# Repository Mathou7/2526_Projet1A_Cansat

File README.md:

# 2526_Projet1A_Cansat

## A Propos de la CanSat
Le concours CanSat, organisé chaque année dans le cadre du C’Space par le CNES et Planète Sciences, propose aux étudiants de concevoir, construire et faire voler un véritable mini-satellite de la taille d’une canette.
Lancé depuis un drone à environ 150 mètres d’altitude, le CanSat doit réaliser une mission scientifique ou technique en chute contrôlée, tout en respectant des contraintes strictes de taille, de masse et d’autonomie et en réalisant les missions imposées.
Ce concours permet aux étudiants d’aborder concrètement l’ensemble des étapes d’un projet spatial : conception système, intégration électronique, programmation embarquée, gestion de l’énergie et tests.

# L'équipe
- Marin.P
- Pierre-Antoine.R
- Lucas.G
- Arnaud.M
- Mathis.B.

## Liste des fonctionnalités
- Mesure de la pression grâce au baromètre
- Mesure de la distance grâce au TOF
- Utilisation d'un moteur pour actionner un mécanisme
- Prise de vidéo à l'aide de la caméra
- Interrupteur général permettant d'allumer et éteindre la canette

## Choix des composants
- Microcontroleur (stm32g431kbt)
- Baromètre (bnp581)
- Moteur brushless (GA12-N20)
- Centrale inertielle (abandonné) 
- Time of Lights (abandonné)
- Caméra (VC0706)
- Interrupteur

## PCB

PCB à quatre couches constitué de
- STM32G431KBT
- Régulateur 6.5-36V vers 5V
- Régulateur 5V vers 3.3V
- Driver Moteur
- Baromètre
- Interface Jack
- Interface Moteur
- Interface Bouton
- Interface Camera
- Connecteur ST

## Difficultés

Approvisionnement en composants
Nous n'avons pas reçu exactement les composants que l'on souhaitait au départ notamment la caméra qui devait enregistrer les images pendant la chute. Celle à laquelle nous avons eu accès transmet les images par onde radio, permettant de voir directement les images sur un écran extérieur à la canette.

Forme restrictive
La forme particulière du PCB imposée par le volume restreint de la canette et le système d'ouverture du parachute a constitué un frein considérable à la conception du PCB.

Code
Une étude détaillée du fonctionnement du baromètre a été nécessaire afin de coder les différentes fonctions permettant d'aboutir au calcul de l'altitude, ce qui a été très chronophage 

Conception de la canette
Le système d'ouverture du parachute a été le principal défi de conception nous forçant à modifier l'architecture de notre canette.

## Solutions trouvées

Les composants 
Pour la caméra nous avons trouvé une caméra avec un fonctionnement différent de celle initialement prévue.
Nous avons reçu le baromètre déjà soudé sur un PCB alors que nous avions demandé le baromètre seul, nous l'avons donc désoudé pour le resouder sur notre PCB.
En attendant la livraison du connecteur pour la batterie (JST-SH) nous avons soudé directement la batterie à l'interface prévue initialement pour le connecteur.

Conception de la canette 
Nous avons séparé notre canette en 2 espaces : une partie acceuillant le PCB et ses différents composants dont le moteur et une partie dans laquelle se trouve le parachute.
Le système d'ouverture fonctionne gràce à 2 goupilles qui maintiennent la partie contenant le parachute et la patie contenant le PCB ensemble. Ces 2 goupilles sont reliées par des fils au moteur qui en tournant va enrouler ces fils autour de son axe et les libérer. Le capuchon dans lequel se trouve le parachute va donc se détacher pour laisser le parachute sortir et se déployer. Le capuchon une fois détaché du reste de la canette reste relié à celle-ci via un autre fil nous permettant de respecter une exigeance imposée par le concours: aucune partie de la canette ne doit tomber au sol sans être ralentie.

## Partie Méca

Partie contenant le PCB et tout les éléments qui y sont reliés :

Opercule fermant la partie PCB qui maintient la partie parachute :

Corps du capuchon contenant le parachute : 

Opercule fermant le capuchon du parachute :

## Bilan des fonctionnalités

Test du bouton permettant d'allumer la LED

https://github.com/user-attachments/assets/89bd5818-fe06-4b41-a8be-61a60c13a220

Test du moteur

https://github.com/user-attachments/assets/85a999e9-10d9-4074-9609-f378fe4b467d

## Reflexion responsable 
Dans quelle mesure votre projet peut-il être intégré à des mesures d’adaptaton ou d’aténuaton du changement
climatque ?

Notre Cansat pourrait filmer un territoire pendant le largage et nous y montrer une évolution. Par exemple, face à une forêt, voir l'effet d'une déforestation ou d'une dégradation du territoire.

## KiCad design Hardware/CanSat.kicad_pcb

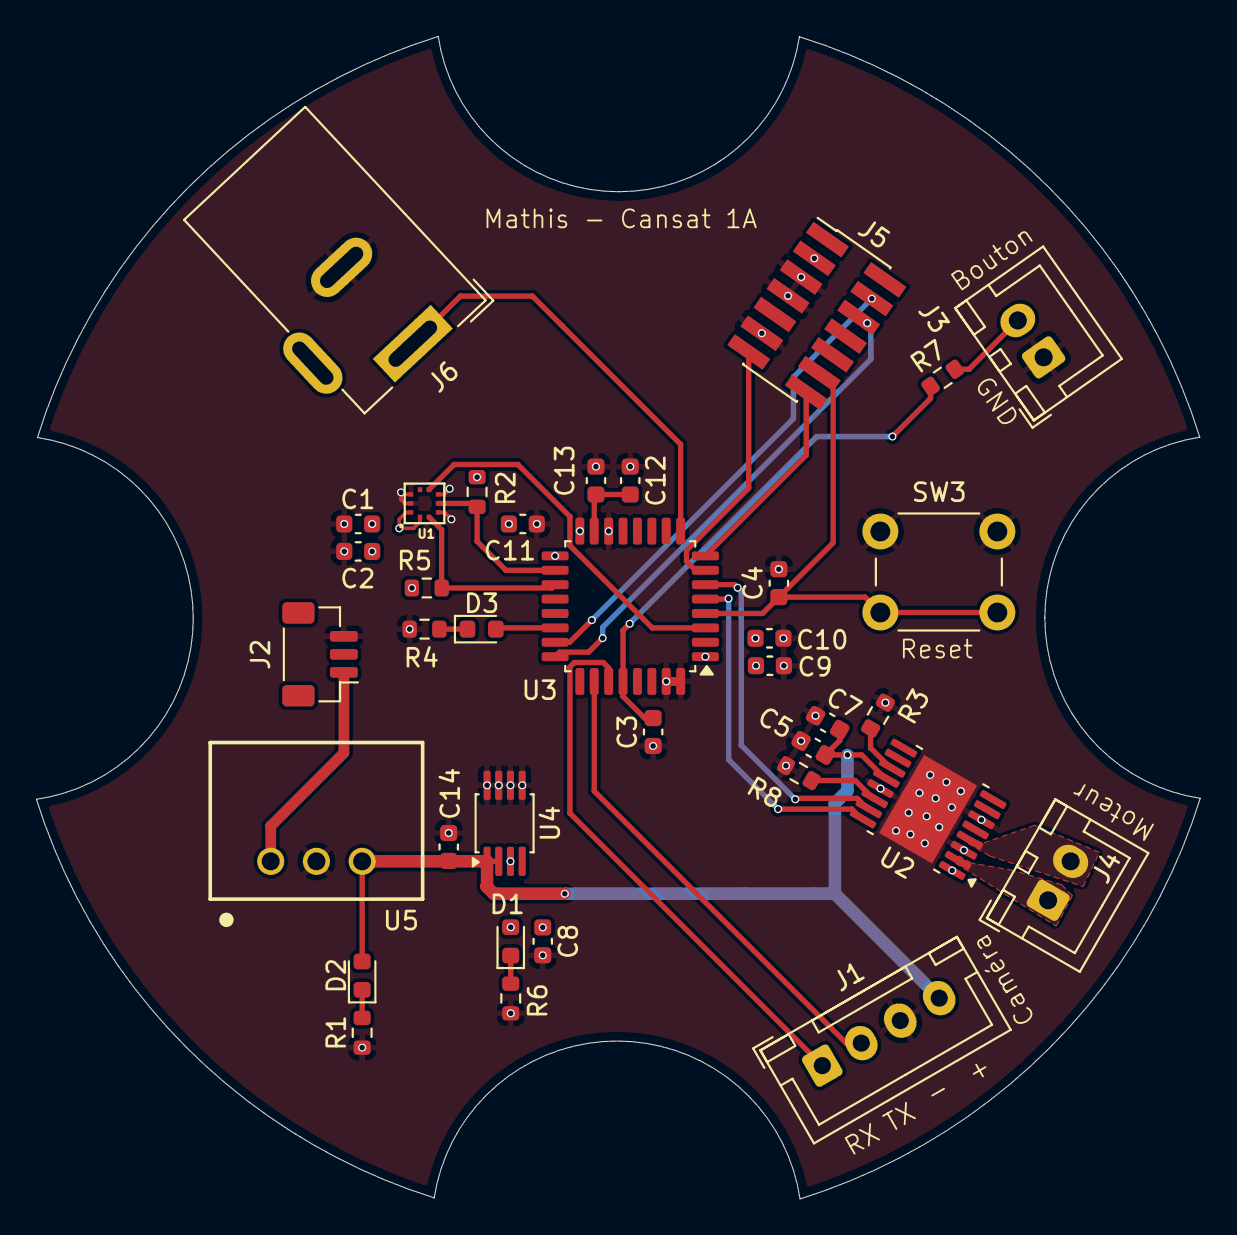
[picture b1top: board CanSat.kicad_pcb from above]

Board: 4 copper layers, 64.7 x 64.6 mm, 36 parts (0 on the bottom side), 28 nets.

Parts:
C1, C2, C3, C4, C5, C10, C11: 100nF; C_0603_1608Metric
C7: 10uF; C_0603_1608Metric
C8, C13, C14: 1uF; C_0603_1608Metric
C9: 4.7uF; C_0603_1608Metric
C12: 10nF; C_0603_1608Metric
D1, D2, D3: LED_Small; LED_0603_1608Metric
J1: Conn_01x04; JST_XH_B4B-XH-A_1x04_P2.50mm_Vertical
J2: Conn_01x03; JST_SH_BM03B-SRSS-TB_1x03-1MP_P1.00mm_Vertical
J3, J4: Conn_01x02; JST_XH_B2B-XH-A_1x02_P2.50mm_Vertical
J5: Conn_ST_STDC14; PinHeader_2x07_P1.27mm_Vertical_SMD
J6: Barrel_Jack_Switch; BarrelJack_Wuerth_6941xx301002
R1, R5, R6: 1k; R_0603_1608Metric
R2, R3, R4, R8: 10k; R_0603_1608Metric
R7: 100; R_0603_1608Metric
SW3: SW_Push; SW_PUSH_6mm_H5mm
U1: BMP581
U2: DRV8833PWP; HTSSOP-16-1EP_4.4x5mm_P0.65mm_EP3.4x5mm_Mask2.46x2.31mm_The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
U3: STM32G431KBTx; LQFP-32_7x7mm_P0.8mm
U4: MIC5219-3.3YMM; MSOP-8_3x3mm_P0.65mm
U5: WPME-FDSM_SIP-3; WPME-FDSM_173010X78

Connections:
+3.3V: C1.2, C2.2, C8.1, C9.2, C10.2, C11.2, D1.2 (A), J5.3 (VCC), R2.2, R4.2, U1.1 (VDDIO), U1.10 (VDD), U2.1 (VREF), U3.1 (VDD), U3.17 (VDD), U4.3 (OUT)
+3.3VA: C12.2, C13.2, U3.15 (VDDA)
+5V: C5.2, C7.1, C14.1, D2.2 (A), J1.4, U2.12 (VM), U4.1 (EN), U4.2 (IN), U5.3
AIN1: U2.16 (AIN1), U3.5 (PA0)
AIN2: U2.15 (AIN2), U3.6 (PA1)
AOUT1: J4.1, U2.2 (AOUT1)
AOUT2: J4.2, U2.4 (AOUT2)
Bouton: C3.2, R7.1, U3.28 (PB5)
GND: C1.1, C2.1, C3.1, C4.2, C5.1, C7.2, C8.2, C9.1, C10.1, C11.1, C12.1, C13.1, C14.2, J1.3, J2.3, J3.1, J5.5 (GND), J5.7 (GND), J5.11 (GNDDetect), J6.2, R1.1, R3.2, R5.1, R6.1, R8.2, SW3.1, U1.3 (GND), U1.5 (SDO/ADR), U1.8 (GND), U1.9 (GND), U2.3 (GND), U2.6 (GND), U2.13 (GND), U2.17 (GND), U3.14 (VSSA), U3.16 (VSS), U3.31 (PB8), U3.32 (VSS), U4.5 (GND), U4.6 (GND), U4.7 (GND), U4.8 (GND), U5.2
INT: U1.6 (CSB), U3.3 (PF1)
JackIN: J6.1, U3.9 (PA4)
NRST: C4.1, J5.12 (~RST), SW3.2, U3.4 (PG10)
unnamed: D1.1 (K), R6.2
unnamed: D2.1 (K), R1.2
unnamed: D3.2 (A), U3.22 (PA12)
unnamed: D3.1 (K), R5.2
unnamed: J3.2, R7.2
unnamed: R8.1, U2.14 (AIPROPI)
unnamed: R3.1, U2.11 (BIPROPI)
RXCAM: J1.1, U3.27 (PB4)
SCL: R4.1, U1.2 (SCK/SCL), U3.19 (PA9)
SDA: R2.1, U1.4 (SDI/SDA), U3.18 (PA8)
SWCLK: J5.6 (JCLK/SWCLK), U3.24 (PA14)
SWDIO: J5.4 (JTMS/SWDIO), U3.23 (PA13)
TXCAM: J1.2, U3.26 (PB3)
VCP_RX: J5.13 (VCP_RX), U3.7 (PA2)
VCP_TX: J5.14 (VCP_TX), U3.8 (PA3)
VIN: J2.1, U5.1

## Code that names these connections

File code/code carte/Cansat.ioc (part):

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Mcu.Name=STM32L431C(B-C)Tx
Mcu.Package=LQFP48
Mcu.UserName=STM32L431CBTx
PA10.Mode=I2C
PA10.Signal=I2C1_SDA
PA2.Mode=Asynchronous
PA2.Signal=USART2_TX
PA3.Mode=Asynchronous
PA3.Signal=USART2_RX
PA9.Mode=I2C
PA9.Signal=I2C1_SCL
PB5.Signal=GPXTI5
RCC.HSE_VALUE=8000000
board=custom

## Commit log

2026-02-05 Update README Ajout fonctionnalités et composants
    Ajout du à propos, de la liste des fonctionnalités et du choix des composants
2026-02-10 création du planning
    Première ébauche du planning à venir
2026-02-19 Create Caméra modèle
2026-02-19 Update and rename Caméra modèle to Caméra modèle et problème
2026-02-19 Update Datasheets
    Ajout des datasheets de la STM, du baromètre, de la centrale inertielle et du driver moteur
2026-02-19 Create STM potentielle
2026-03-12 base du code
2026-03-19 Ajout Datasheet du micropro
2026-03-19 Ajout de datasheet
2026-03-19 Create code arduino caméra
2026-03-19 datasheet news
2026-03-19 Create code C caméra gemini
2026-03-19 implémentation caméra
2026-03-26 Update code C caméra gemini
2026-04-09 Ajout BOM
    Ajout de la fiche contenant tout les composants nécessaires au PCB
2026-04-16 Upload Kicad files
2026-05-05 update code
    Rajout de l'entièreté du code du baromètre
2026-05-07 Amélioration du ReadME
    Updated project description and team members in README.md. Added details about the CanSat competition and PCB components.
2026-05-20 Débogage code
2026-05-29 Update README.md
    readme avancé
2026-05-31 Correction d'erreurs et amélioration README
